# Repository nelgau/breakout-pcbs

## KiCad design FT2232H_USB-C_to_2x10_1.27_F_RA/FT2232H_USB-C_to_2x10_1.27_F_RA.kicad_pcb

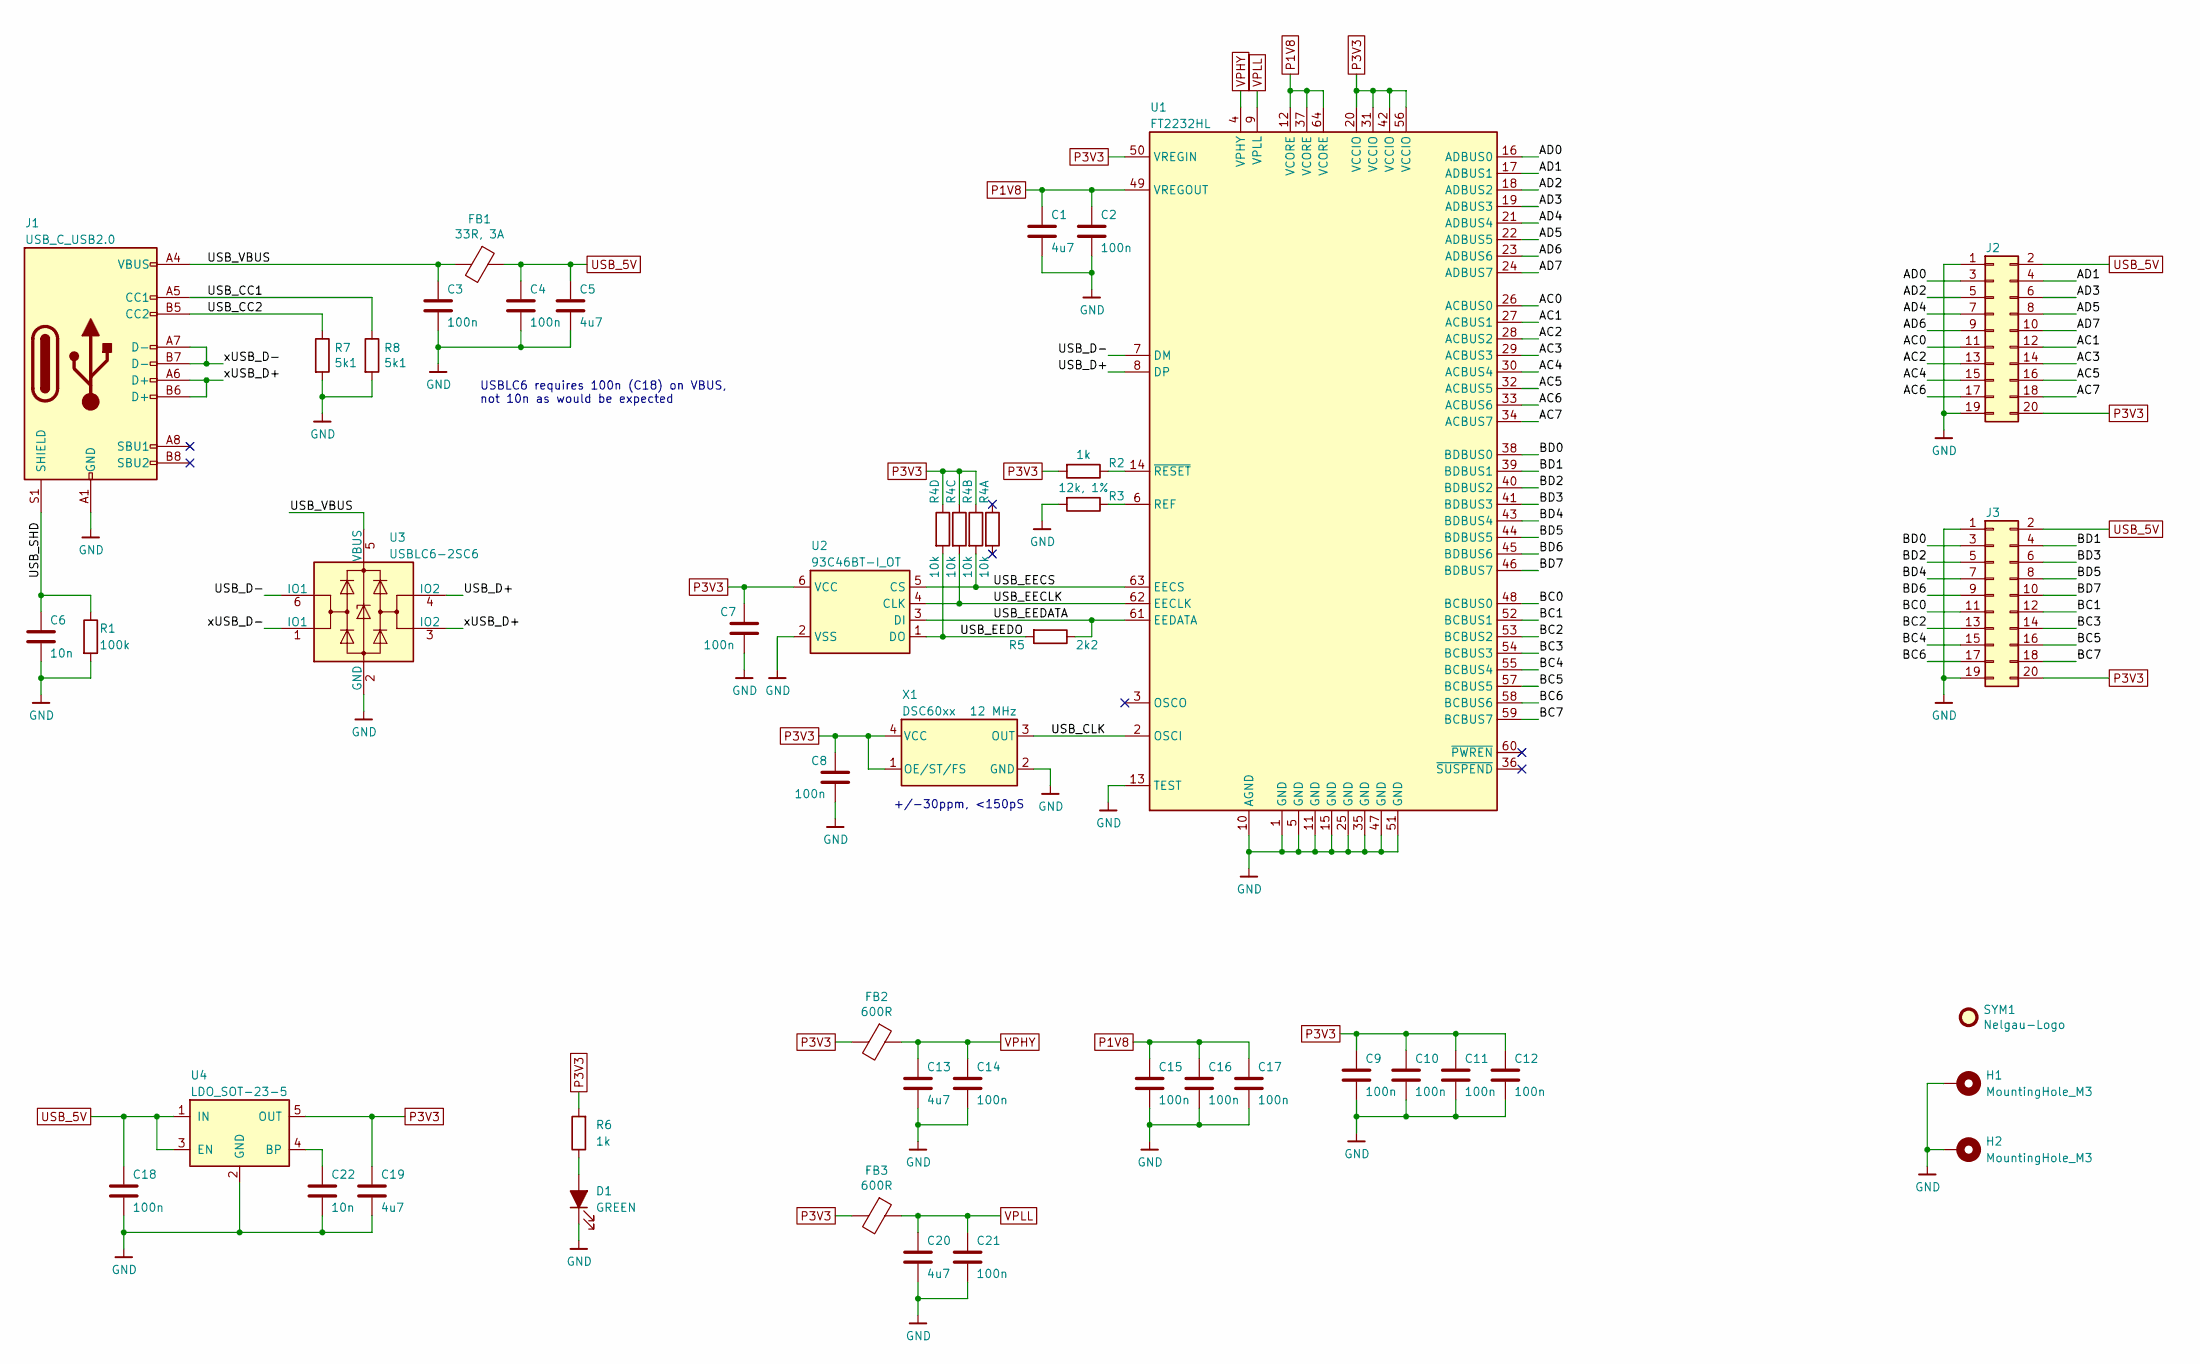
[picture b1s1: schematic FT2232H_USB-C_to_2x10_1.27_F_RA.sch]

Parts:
C1, C5, C13, C19, C20: 4u7; C_0603_1608Metric
C2, C3, C4, C7, C8, C9, C10, C11, C12, C14, C15, C16, C17, C18, C21: 100n; C_0603_1608Metric
C6, C22: 10n; C_0603_1608Metric
D1: GREEN; LED_0603_1608Metric
FB1: 33R, 3A; L_0603_1608Metric; MPN BLM18PG330SN1D
FB2, FB3: 600R; L_0603_1608Metric
H1, H2: MountingHole_M3; MountingHole_3.2mm_M3_Pad_Via
J1: USB_C_USB2.0; USB_C_Receptacle_HRO_TYPE-C-31-M-12
J2, J3: Conn_02x10_Odd_Even; PinSocket_2x10_P2.54mm_Horizontal
R1: 100k; R_0603_1608Metric; MPN RC0603JR-07100KL
R2, R6: 1k; R_0603_1608Metric
R3: 12k, 1%; R_0603_1608Metric
R4: 10k; R_Array_Convex_4x0603; MPN YC164-JR-0710KL
R5: 2k2; R_0603_1608Metric
R7, R8: 5k1; R_0603_1608Metric
SYM1: Nelgau-Logo; Nelgau-Logo_5.2x1.7mm_SilkScreen
U1: FT2232HL; LQFP-64_10x10mm_P0.5mm
U2: 93C46BT-I_OT; SOT-23-6
U3: USBLC6-2SC6; SOT-23-6
U4: LDO_SOT-23-5; SOT-23-5
X1: DSC60xx; Oscillator_2.5x2.0

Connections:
/AC0: J2.11, U1.26 (ACBUS0)
/AC1: J2.12, U1.27 (ACBUS1)
/AC2: J2.13, U1.28 (ACBUS2)
/AC3: J2.14, U1.29 (ACBUS3)
/AC4: J2.15, U1.30 (ACBUS4)
/AC5: J2.16, U1.32 (ACBUS5)
/AC6: J2.17, U1.33 (ACBUS6)
/AC7: J2.18, U1.34 (ACBUS7)
/AD0: J2.3, U1.16 (ADBUS0)
/AD1: J2.4, U1.17 (ADBUS1)
/AD2: J2.5, U1.18 (ADBUS2)
/AD3: J2.6, U1.19 (ADBUS3)
/AD4: J2.7, U1.21 (ADBUS4)
/AD5: J2.8, U1.22 (ADBUS5)
/AD6: J2.9, U1.23 (ADBUS6)
/AD7: J2.10, U1.24 (ADBUS7)
/BC0: J3.11, U1.48 (BCBUS0)
/BC1: J3.12, U1.52 (BCBUS1)
/BC2: J3.13, U1.53 (BCBUS2)
/BC3: J3.14, U1.54 (BCBUS3)
/BC4: J3.15, U1.55 (BCBUS4)
/BC5: J3.16, U1.57 (BCBUS5)
/BC6: J3.17, U1.58 (BCBUS6)
/BC7: J3.18, U1.59 (BCBUS7)
/BD0: J3.3, U1.38 (BDBUS0)
/BD1: J3.4, U1.39 (BDBUS1)
/BD2: J3.5, U1.40 (BDBUS2)
/BD3: J3.6, U1.41 (BDBUS3)
/BD4: J3.7, U1.43 (BDBUS4)
/BD5: J3.8, U1.44 (BDBUS5)
/BD6: J3.9, U1.45 (BDBUS6)
/BD7: J3.10, U1.46 (BDBUS7)
/USB_CC1: J1.A5 (CC1), R8.1
/USB_CC2: J1.B5 (CC2), R7.1
/USB_CLK: U1.2 (OSCI), X1.3 (OUT)
/USB_D+: U1.8 (DP), U3.4 (IO2)
/USB_D-: U1.7 (DM), U3.6 (IO1)
/USB_EECLK: R4.3, U1.62 (EECLK), U2.4 (CLK)
/USB_EECS: R4.2, U1.63 (EECS), U2.5 (CS)
/USB_EEDATA: R5.1, U1.61 (EEDATA), U2.3 (DI)
/USB_EEDO: R4.4, R5.2, U2.1 (DO)
/USB_SHD: C6.1, J1.S1 (SHIELD), R1.1
/USB_VBUS: C3.1, FB1.2, J1.A4 (VBUS), J1.A9 (VBUS), J1.B4 (VBUS), J1.B9 (VBUS), U3.5 (VBUS)
/xUSB_D+: J1.A6 (D+), J1.B6 (D+), U3.3 (IO2)
/xUSB_D-: J1.A7 (D-), J1.B7 (D-), U3.1 (IO1)
GND: C1.2, C2.2, C3.2, C4.2, C5.2, C6.2, C7.2, C8.2, C9.2, C10.2, C11.2, C12.2, C13.2, C14.2, C15.2, C16.2, C17.2, C18.2, C19.2, C20.2, C21.2, C22.2, D1.1 (K), H1.1, H2.1, J1.A1 (GND), J1.A12 (GND), J1.B1 (GND), J1.B12 (GND), J2.1, J2.19, J3.1, J3.19, R1.2, R3.2, R7.2, R8.2, U1.1 (GND), U1.5 (GND), U1.10 (AGND), U1.11 (GND), U1.13 (TEST), U1.15 (GND), U1.25 (GND), U1.35 (GND), U1.47 (GND), U1.51 (GND), U2.2 (VSS), U3.2 (GND), U4.2 (GND), X1.2 (GND)
unnamed: C22.1, U4.4 (BP)
unnamed: D1.2 (A), R6.1
unnamed: R2.1, U1.14 (~RESET)
unnamed: R3.1, U1.6 (REF)
P1V8: C1.1, C2.1, C15.1, C16.1, C17.1, U1.12 (VCORE), U1.37 (VCORE), U1.49 (VREGOUT), U1.64 (VCORE)
P3V3: C7.1, C8.1, C9.1, C10.1, C11.1, C12.1, C19.1, FB2.2, FB3.2, J2.20, J3.20, R2.2, R4.5, R4.6, R4.7, R6.2, U1.20 (VCCIO), U1.31 (VCCIO), U1.42 (VCCIO), U1.50 (VREGIN), U1.56 (VCCIO), U2.6 (VCC), U4.5 (OUT), X1.1 (OE/ST/FS), X1.4 (VCC)
USB_5V: C4.1, C5.1, C18.1, FB1.1, J2.2, J3.2, U4.1 (IN), U4.3 (EN)
VPHY: C13.1, C14.1, FB2.1, U1.4 (VPHY)
VPLL: C20.1, C21.1, FB3.1, U1.9 (VPLL)

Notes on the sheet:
USBLC6 requires 100n (C18) on VBUS, not 10n as would be expected
+/-30ppm, <150pS

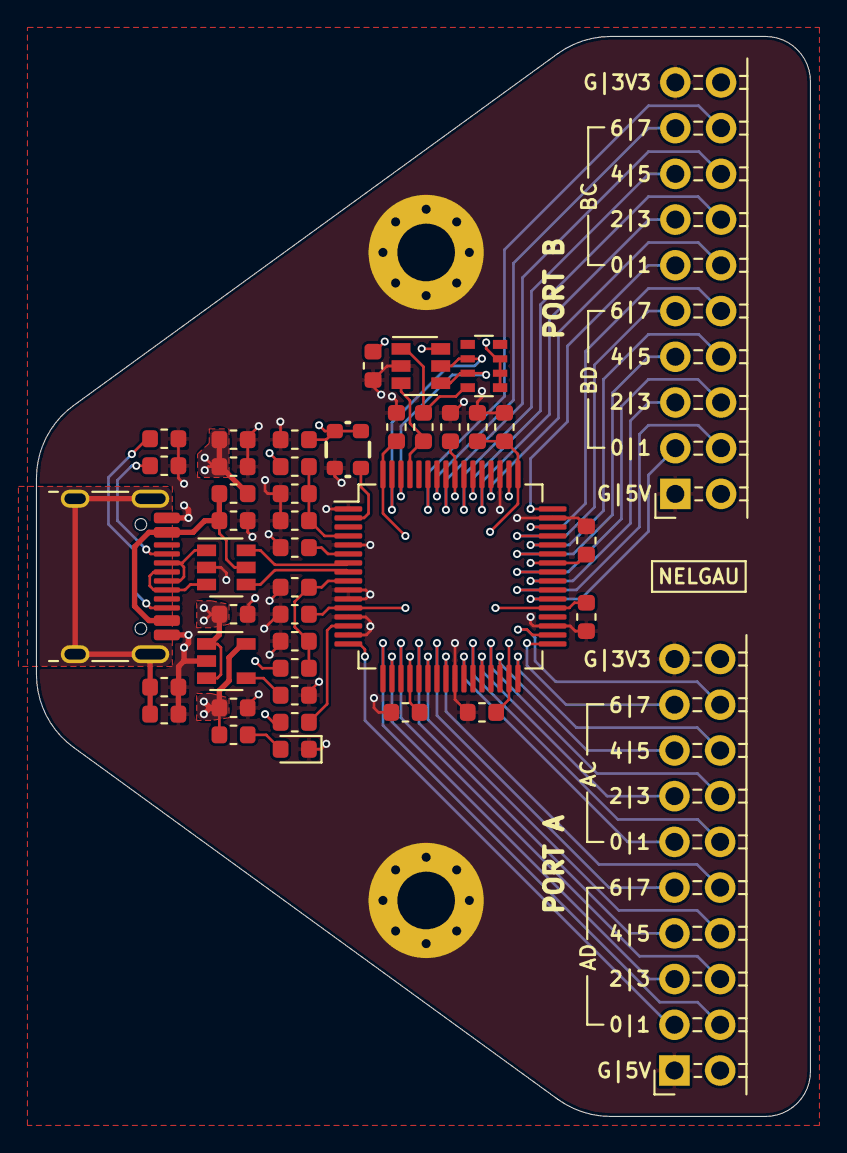
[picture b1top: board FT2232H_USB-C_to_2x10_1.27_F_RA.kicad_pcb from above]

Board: 4 copper layers, 43.0 x 60.0 mm, 45 parts (0 on the bottom side), 55 nets.

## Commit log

2020-06-23 Added personal KiCad libraries as a submodule lib/nelgau
2020-06-23 Add typical KiCad .gitignore
2020-06-23 Adapter board, 2x5 P2.54mm F RA to P1.27mm M, for JTAG, SWD, Lattice ISP programming interface
2020-06-23 Update 'nelgau' libraries submodule
2020-06-23 [lib][ftp] Add variant of 2x5 2.54mm RA header without overhanging silkscreen
2020-06-23 Add 'header_2x5_2.54_F_RA_to_1.27_M' adapter board
2020-06-25 Update 'nelgau' library submodule
2020-06-25 Update FTSH footprint with polarity mark
2020-07-08 Progress towards 2x5 P2.54mm F RA to P1.27mm M
2020-07-09 Create FT2232H_USB-C_to_2x10_1.27_F_RA breakout project
2020-07-21 Import old ice-programmer design into FT2232H_USB-C breakout
2020-07-21 Initial placement for FT2232H_USB-C
2020-07-22 Adjusting placement for FT2232_USB-C
2020-07-22 Add Nelgau-Logo to FT2232H_USB-C
2020-07-23 Routed all dense nets near FT2232H
2020-07-23 Add tentative board edge and trim pin socket footprints
2020-07-24 Set final pin socket clearance
2020-07-24 Clean up layout around FT2232H
2020-07-24 Rough routing of data and control output buses
2020-07-24 Finish routing data and control buses
2020-07-24 Rough in the board edge with arcs
2020-07-25 Use USB-C connector instead of micro-USB
2020-07-25 Reduce via usage on FT2232 ground connections
2020-07-25 Fix collision between power trace and mouting hole pad
2020-07-25 Implement option to use LDO with bypass capacitor
2020-07-26 Simplify routing of USB 2.0 data lines
2020-07-26 Correct misrouted trace within USB interface
2020-08-15 Poor copper zones and run final DRC checks
2020-09-25 Fix solder mask clearance/minimum width and reexport gerbers
